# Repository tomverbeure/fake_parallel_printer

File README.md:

# Fake Parallel Printer

This repo contains the design files for the Fake Printer tool: a hardware
dongle with a DB-25 connector that plugs into the parallel printer port
that was available on nearly all computers and equipment in the eighties
and nineties.

Check out this blog post for a detailed description of the design,
and build and usage instructions:

* [Fake Parallel Printer - A Parallel Port Traffic Capturing Tool](https://tomverbeure.github.io/2023/01/24/Fake-Parallel-Printer-Capture-Tool-HW.html)

There are 2 versions of the PCB. Revision 2 only uses 2 layers and doesn't
stick out as much out of the device in which is plugged in. It's probably
the best one to build. The firmware is designed to work for both PCB versions.

## PCB v1

* KiCAD database of the PCB: [`./parallel2usb_v1`](./parallel2usb_v1)
* [Schematic of PCB v1](./parallel2usb_v1/parallel2usb_v1_schematic.pdf)

## PCB v2

**WARNING: v2 hasn't been tested!!!**

* KiCAD database of the PCB: [`./parallel2usb_v2`](./parallel2usb_v2)
* [Schematic of PCB v2](./parallel2usb_v2/parallel2usb_v2_schematic.pdf)

A Digikey cart with all the components to populate version 2 of the PCB can
be found [here](https://www.digikey.com/short/mcb8vf27). Not all
resistors and capacitor must be populated though. Check out the blog
post for details.

## Firmware

[`parallel2usb_hd_on.uf2`](parallel2usb_hd_on.uf2) contains the compiled
firmware for the Raspberry Pico.

To make changes and recompile yourself:

* set the `PICO_SDK` environment variable to the path of your locally installed 
  [Raspberry Pico SDK](https://github.com/raspberrypi/pico-sdk).
* Build the code:

      mkdir -p ./c/build
      cd ./c/build
      cmake ..
      make

* If all goes well, a new `parallel2usb.uf2` will be waiting in
  `./c/build/parallel2usb`.

## Capturing Parallel Port Data

* Plug in the board into the host with the parallel port.
* Connect your PC to the board with a USB cable.
* Run `python3 ./fake_printer.py -p <USB serial device>` (Use -h for more options.)
* Issue a print operation on the host.
* A new file will be generated for each print operation

## Converting a Parallel Port Captured File

* PCL: use [Ghostscript](https://ghostscript.com/releases/gpcldnld.html)

    `~/tools/ghostpcl-10.0.0-linux-x86_64/gpcl6-1000-linux-x86_64 -dNOPAUSE -sOutputFile=output.png -sDEVICE=png256 -g8000x8000 -r600x600 print_cap.pcl`

* Epson ESC/P: use [PrinterToPDF](https://github.com/RWAP/PrinterToPDF)

    `/opt/printerToPDF/bin/printerToPDF -o output -f /opt/printerToPDF/lib/PrinterToPDF/font2/Epson-Standard.C16 print_cap.esc_p`

* Encapsulated Postscript: use Ghostscript and ImageMagick to add a background if necessary.  Note that some scopes (TDS 684B) may emit a few chunks of comments that `fake_printer.py` will get with multiple-second delays, and they need to be concatenated together to form a valid `eps` file.

    `gs -dSAFER -dBATCH -dNOPAUSE -dEPSCrop -sDEVICE=pngalpha -r300 -sOutputFile=ph1-zoomout.png ph1-zoomout.eps; convert -background black -alpha remove -alpha off ph1-zoomout.png ph1-zoomout.png`

# Conversions

* HP Infinium

```
./fake_printer.py --port=/dev/ttyACM0 -t 2 -v --prefix=hp_osc_ -s eps
inkscape -f ./hp_osc_0.eps -w 1580 -y=255 -e hp_osc_0.png
convert hp_osc_0.png -crop 1294x971+142+80 hp_osc_0_cropped.png
```

* Advantest R3273

    * Config printer: Config -> Copy Config -> Printer: 

    * To print: Copy
    * To convert:

```
./fake_printer.py --port=/dev/ttyACM0 -t 2 -v --prefix=r3273_ -s pcl
~/tools/ghostpcl-10.0.0-linux-x86_64/gpcl6-1000-linux-x86_64 -dNOPAUSE -sOutputFile=test.png -sDEVICE=png256 -g8000x8000 -r600x600 r3273_0.pcl
convert test.png -filter point -resize 2000  test2.png
convert test2.png -crop 640x480+315+94 test3.png
```

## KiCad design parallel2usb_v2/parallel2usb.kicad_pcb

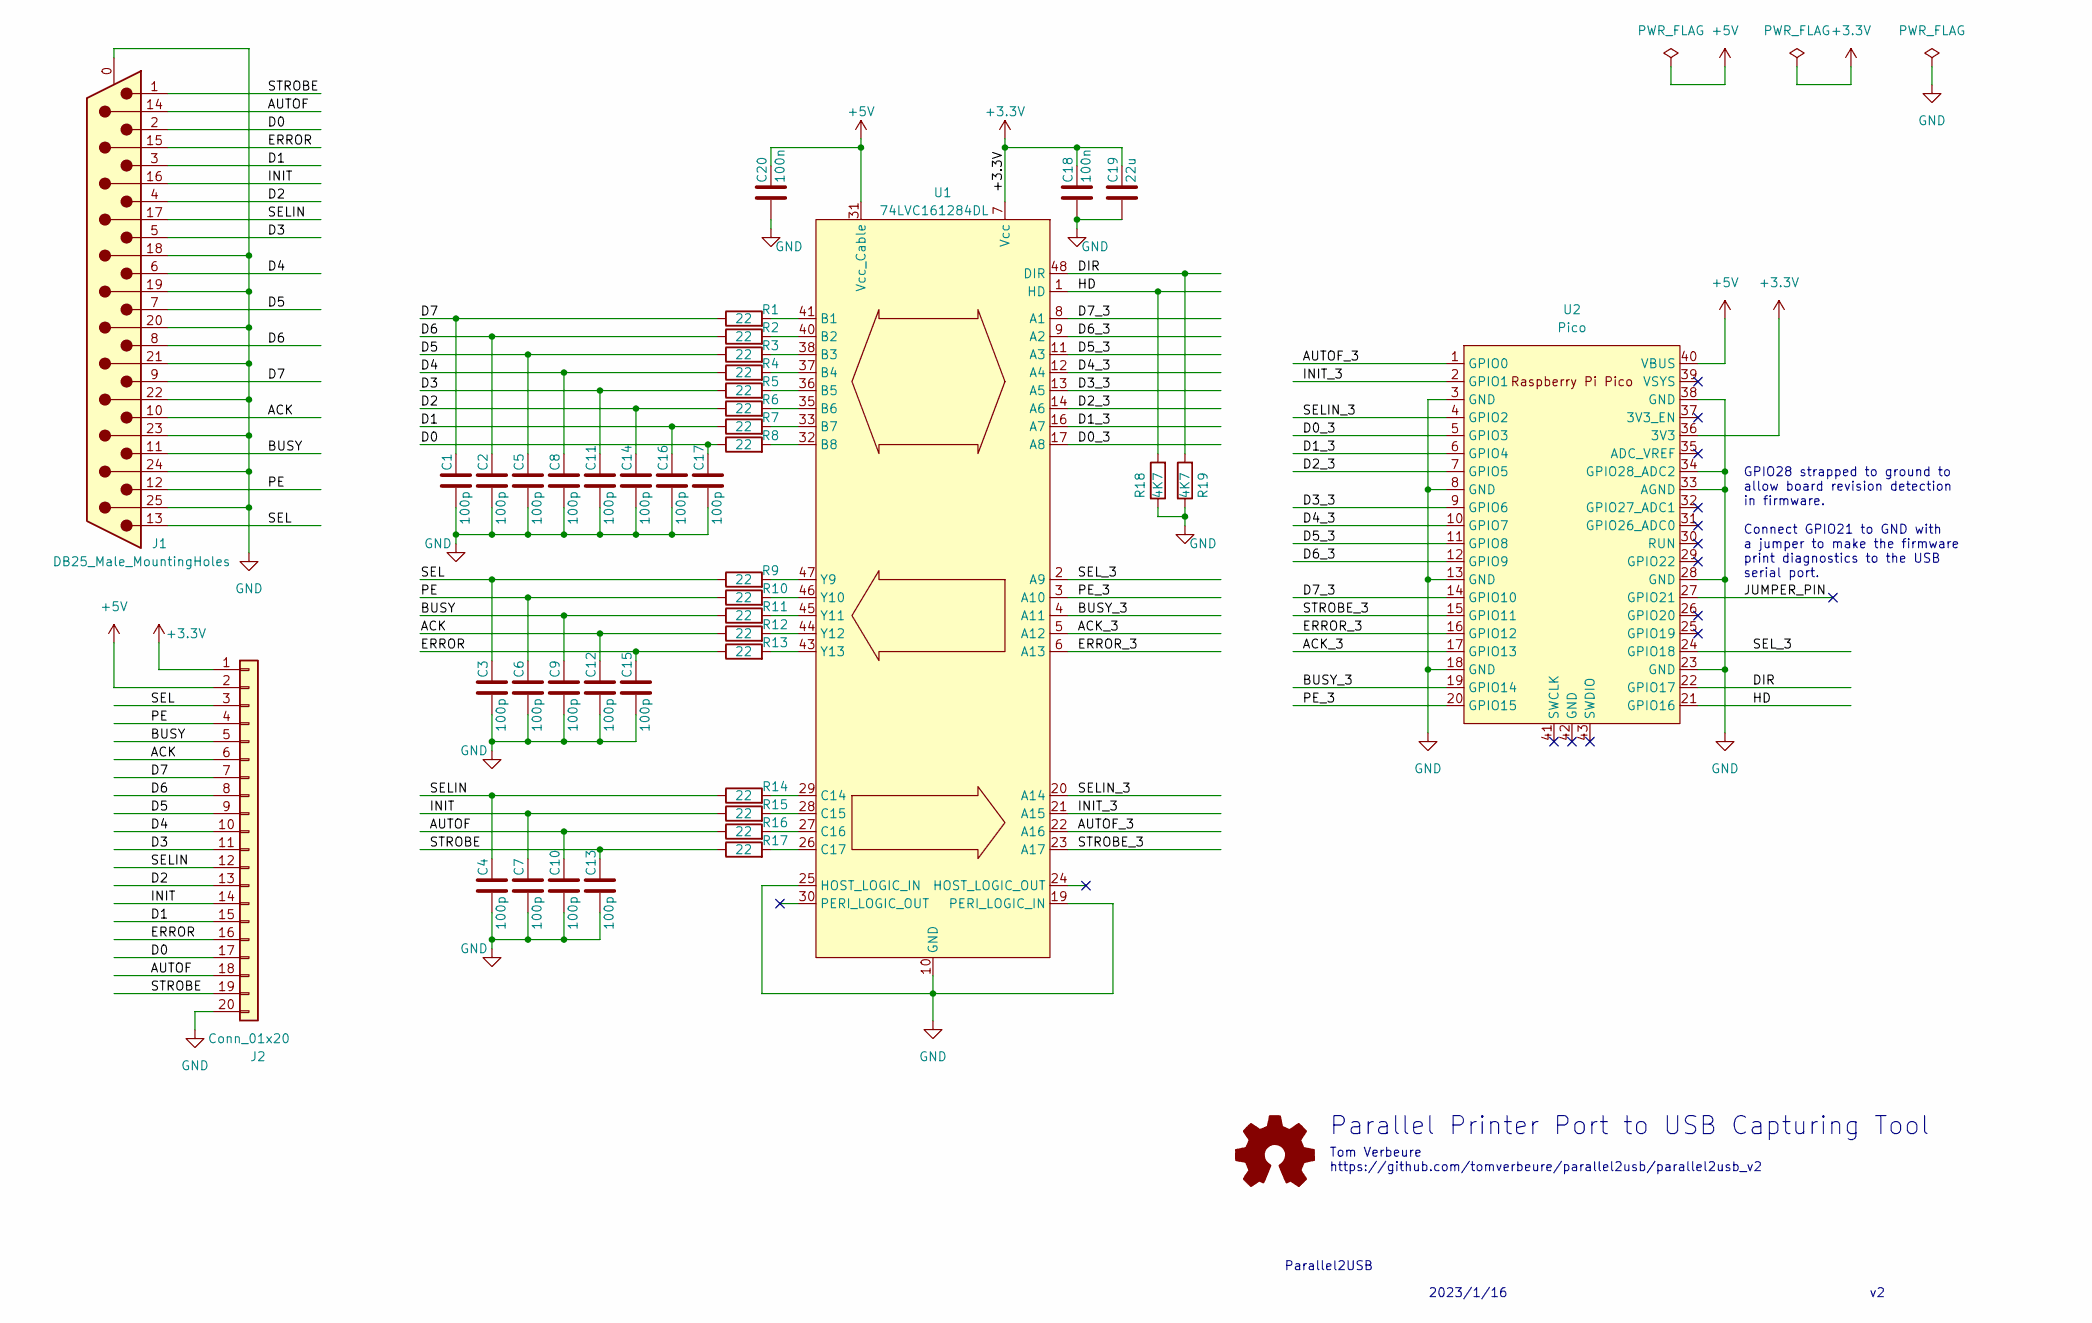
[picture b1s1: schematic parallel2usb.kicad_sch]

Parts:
C1, C2, C3, C4, C5, C6, C7, C8, C9, C10, C11, C12, C13, C14, C15, C16, C17: 100p; C_0603_1608Metric_Pad1.08x0.95mm_HandSolder
C18, C20: 100n; C_0603_1608Metric_Pad1.08x0.95mm_HandSolder
C19: 22u; C_0603_1608Metric_Pad1.08x0.95mm_HandSolder
J1: DB25_Male_MountingHoles; DSUB-25_Male_Horizontal_P2.77x2.84mm_EdgePinOffset7.70mm_Ho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
J2: Conn_01x20; PinHeader_1x20_P2.54mm_Vertical
R1, R2, R3, R4, R5, R6, R7, R8, R9, R10, R11, R12, R13, R14, R15, R16, R17: 22; R_0603_1608Metric_Pad0.98x0.95mm_HandSolder
R18, R19: 4K7; R_0603_1608Metric_Pad0.98x0.95mm_HandSolder
U1: 74LVC161284DL; SSOP-48_7.5x15.9mm_P0.635mm
U2: Pico; RPi_Pico_SMD_TH

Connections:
+3.3V: C18.1, C19.1, J2.1, U1.7 (Vcc), U1.18 (Vcc), U2.36 (3V3)
+5V: C20.1, J2.2, U1.31 (Vcc_Cable), U1.42 (Vcc_Cable), U2.40 (VBUS)
/ACK: C12.1, J1.10, J2.6, R12.1
/ACK_3: U1.5 (A12), U2.17 (GPIO13)
/AUTOF: C10.1, J1.14, J2.18, R16.1
/AUTOF_3: U1.22 (A16), U2.1 (GPIO0)
/BUSY: C9.1, J1.11, J2.5, R11.1
/BUSY_3: U1.4 (A11), U2.19 (GPIO14)
/D0: C17.1, J1.2, J2.17, R8.1
/D0_3: U1.17 (A8), U2.5 (GPIO3)
/D1: C16.1, J1.3, J2.15, R7.1
/D1_3: U1.16 (A7), U2.6 (GPIO4)
/D2: C14.1, J1.4, J2.13, R6.1
/D2_3: U1.14 (A6), U2.7 (GPIO5)
/D3: C11.1, J1.5, J2.11, R5.1
/D3_3: U1.13 (A5), U2.9 (GPIO6)
/D4: C8.1, J1.6, J2.10, R4.1
/D4_3: U1.12 (A4), U2.10 (GPIO7)
/D5: C5.1, J1.7, J2.9, R3.1
/D5_3: U1.11 (A3), U2.11 (GPIO8)
/D6: C2.1, J1.8, J2.8, R2.1
/D6_3: U1.9 (A2), U2.12 (GPIO9)
/D7: C1.1, J1.9, J2.7, R1.1
/D7_3: U1.8 (A1), U2.14 (GPIO10)
/DIR: R19.2, U1.48 (DIR), U2.22 (GPIO17)
/ERROR: C15.1, J1.15, J2.16, R13.1
/ERROR_3: U1.6 (A13), U2.16 (GPIO12)
/HD: R18.2, U1.1 (HD), U2.21 (GPIO16)
/INIT: C7.1, J1.16, J2.14, R15.1
/INIT_3: U1.21 (A15), U2.2 (GPIO1)
/JUMPER_PIN: U2.27 (GPIO21)
/PE: C6.1, J1.12, J2.4, R10.1
/PE_3: U1.3 (A10), U2.20 (GPIO15)
/SEL: C3.1, J1.13, J2.3, R9.1
/SELIN: C4.1, J1.17, J2.12, R14.1
/SELIN_3: U1.20 (A14), U2.4 (GPIO2)
/SEL_3: U1.2 (A9), U2.24 (GPIO18)
/STROBE: C13.1, J1.1, J2.19, R17.1
/STROBE_3: U1.23 (A17), U2.15 (GPIO11)
GND: C1.2, C2.2, C3.2, C4.2, C5.2, C6.2, C7.2, C8.2, C9.2, C10.2, C11.2, C12.2, C13.2, C14.2, C15.2, C16.2, C17.2, C18.2, C19.2, C20.2, J1.0 (PAD), J1.18, J1.19, J1.20, J1.21, J1.22, J1.23, J1.24, J1.25, J2.20, R18.1, R19.1, U1.10 (GND), U1.15 (GND), U1.19 (PERI_LOGIC_IN), U1.25 (HOST_LOGIC_IN), U1.34 (GND), U1.39 (GND), U2.3 (GND), U2.8 (GND), U2.13 (GND), U2.18 (GND), U2.23 (GND), U2.28 (GND), U2.33 (AGND), U2.34 (GPIO28_ADC2), U2.38 (GND)
unnamed: R1.2, U1.41 (B1)
unnamed: R2.2, U1.40 (B2)
unnamed: R3.2, U1.38 (B3)
unnamed: R4.2, U1.37 (B4)
unnamed: R5.2, U1.36 (B5)
unnamed: R6.2, U1.35 (B6)
unnamed: R7.2, U1.33 (B7)
unnamed: R8.2, U1.32 (B8)
unnamed: R9.2, U1.47 (Y9)
unnamed: R10.2, U1.46 (Y10)
unnamed: R11.2, U1.45 (Y11)
unnamed: R12.2, U1.44 (Y12)
unnamed: R13.2, U1.43 (Y13)
unnamed: R14.2, U1.29 (C14)
unnamed: R15.2, U1.28 (C15)
unnamed: R16.2, U1.27 (C16)
unnamed: R17.2, U1.26 (C17)

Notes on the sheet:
Parallel2USB
2023/1/16
Connect GPIO21 to GND with a jumper to make the firmware print diagnostics to the USB serial port.
GPIO28 strapped to ground to allow board revision detection in firmware.
Tom Verbeure https://github.com/tomverbeure/parallel2usb/parallel2usb_v2
Parallel Printer Port to USB Capturing Tool

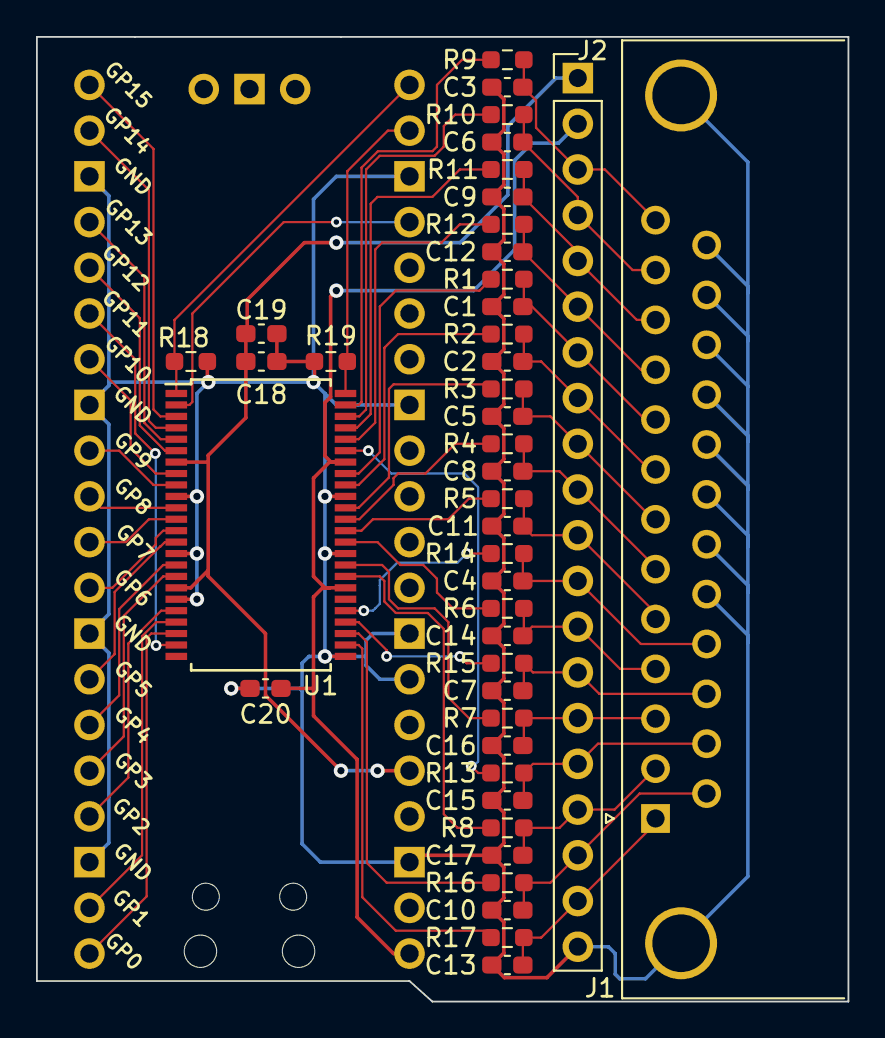
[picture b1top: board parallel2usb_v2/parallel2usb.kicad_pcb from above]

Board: 2 copper layers, 45.1 x 53.6 mm, 43 parts (1 on the bottom side), 56 nets.

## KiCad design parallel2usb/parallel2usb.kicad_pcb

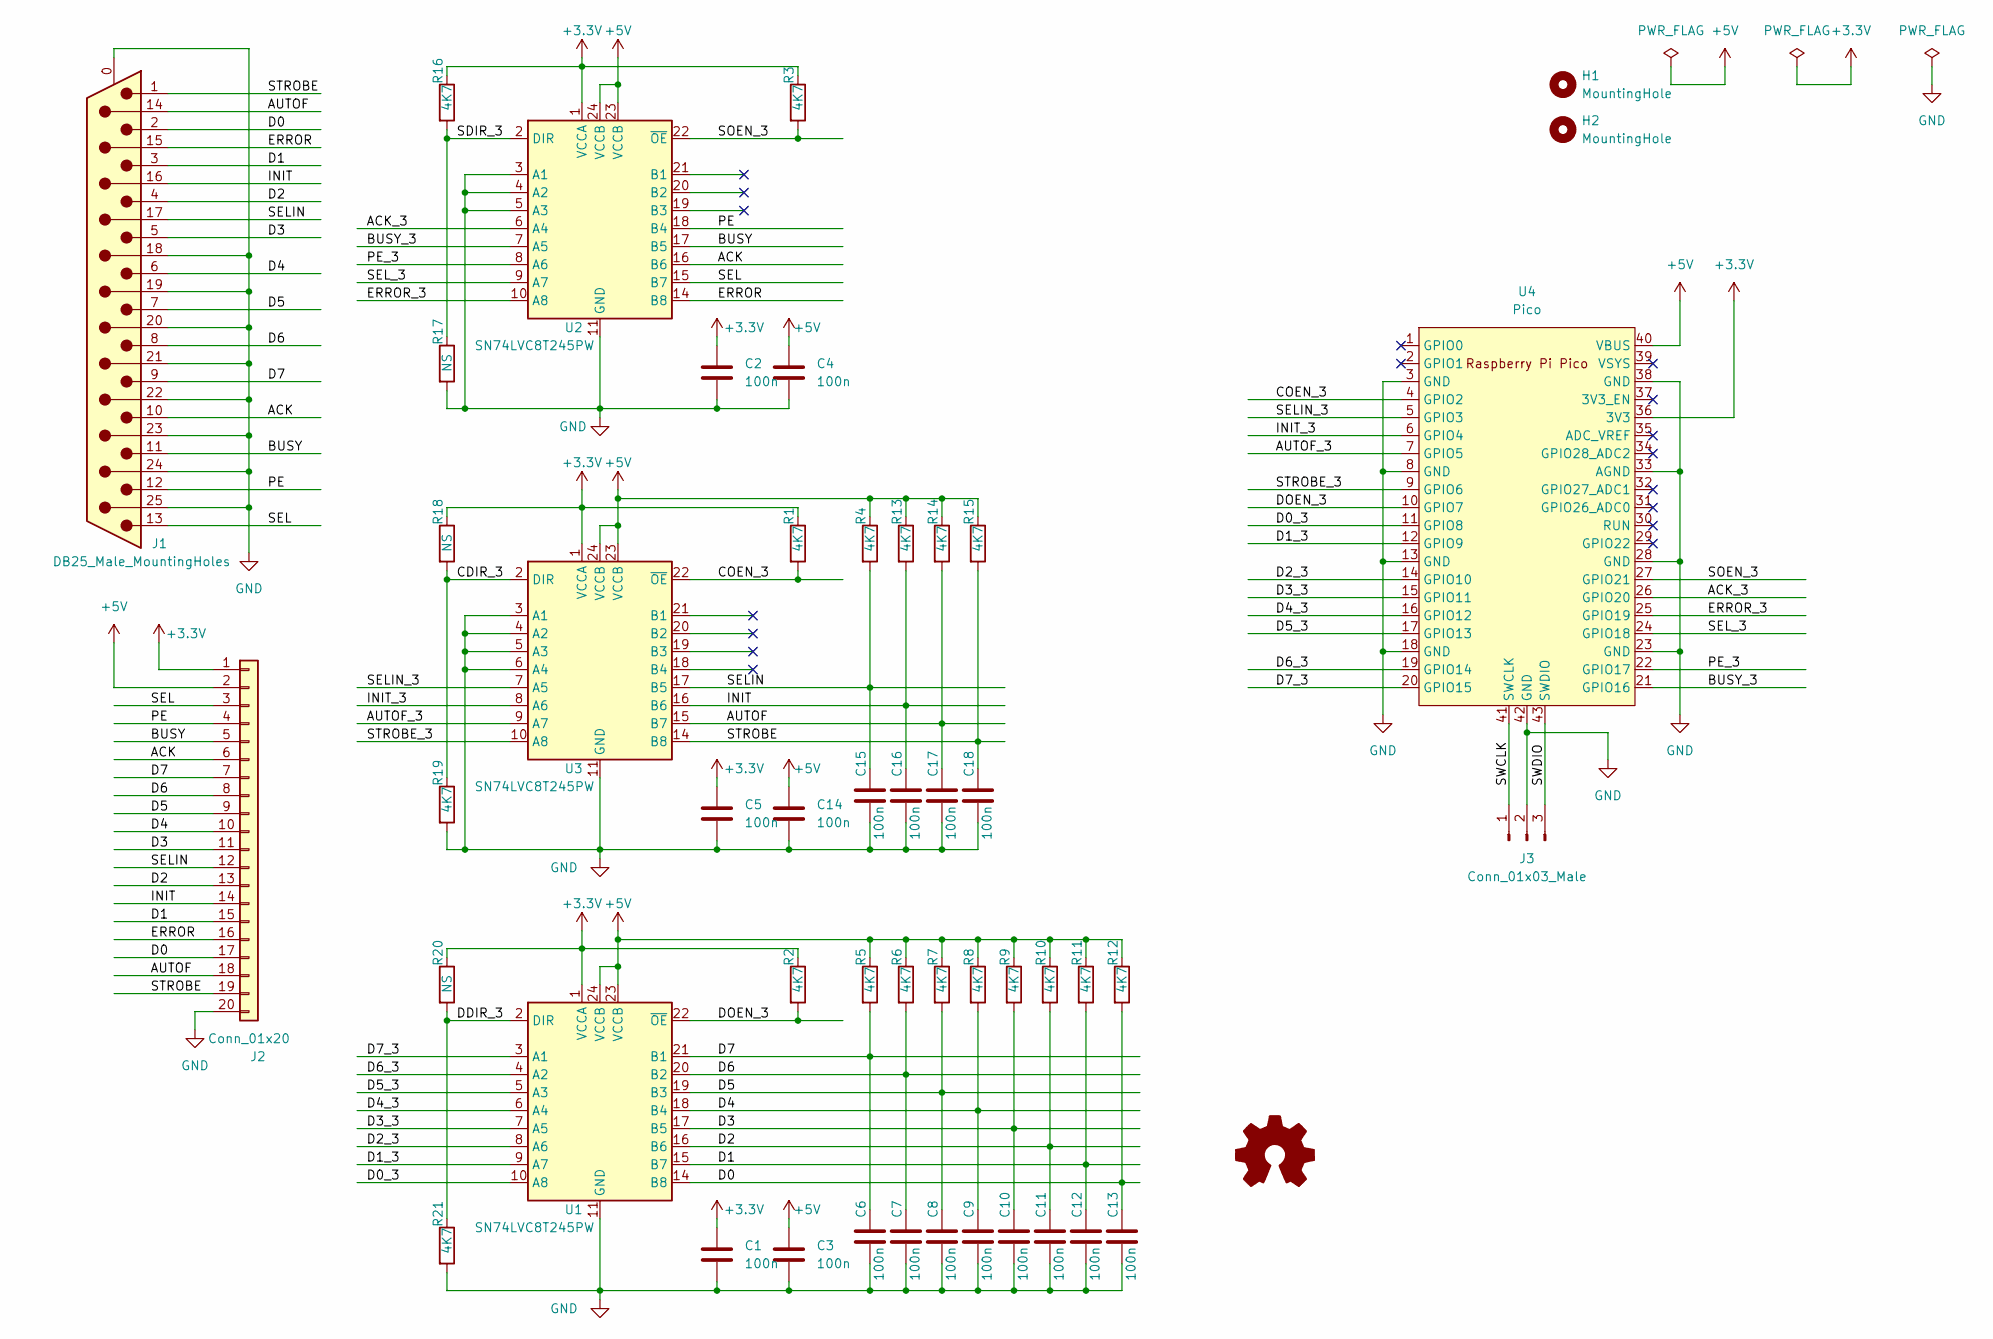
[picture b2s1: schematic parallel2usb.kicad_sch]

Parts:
C1, C2, C3, C4, C5, C6, C7, C8, C9, C10, C11, C12, C13, C14, C15, C16, C17, C18: 100n; C_0603_1608Metric_Pad1.08x0.95mm_HandSolder
H1, H2: MountingHole; MountingHole_2.7mm_M2.5
J1: DB25_Male_MountingHoles; DSUB-25_Male_Horizontal_P2.77x2.84mm_EdgePinOffset7.70mm_Ho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
J2: Conn_01x20; PinHeader_1x20_P2.54mm_Vertical
J3: Conn_01x03_Male; PinHeader_1x03_P2.54mm_Vertical
R1, R2, R3, R4, R5, R6, R7, R8, R9, R10, R11, R12, R13, R14, R15, R16, R19, R21: 4K7; R_0603_1608Metric_Pad0.98x0.95mm_HandSolder
R17, R18, R20: NS; R_0603_1608Metric_Pad0.98x0.95mm_HandSolder
U1, U2, U3: SN74LVC8T245PW; TSSOP-24_4.4x7.8mm_P0.65mm
U4: Pico; RPi_Pico_SMD_TH

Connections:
+3.3V: C1.1, C2.1, C5.1, J2.1, R1.1, R2.1, R3.1, R16.1, R18.1, R20.1, U1.1 (VCCA), U2.1 (VCCA), U3.1 (VCCA), U4.36 (3V3)
+5V: C3.1, C4.1, C14.1, J2.2, R4.1, R5.1, R6.1, R7.1, R8.1, R9.1, R10.1, R11.1, R12.1, R13.1, R14.1, R15.1, U1.23 (VCCB), U1.24 (VCCB), U2.23 (VCCB), U2.24 (VCCB), U3.23 (VCCB), U3.24 (VCCB), U4.40 (VBUS)
/ACK: J1.10, J2.6, U2.16 (B6)
/ACK_3: U2.6 (A4), U4.26 (GPIO20)
/AUTOF: C17.1, J1.14, J2.18, R14.2, U3.15 (B7)
/AUTOF_3: U3.9 (A7), U4.7 (GPIO5)
/BUSY: J1.11, J2.5, U2.17 (B5)
/BUSY_3: U2.7 (A5), U4.21 (GPIO16)
/CDIR_3: R18.2, R19.1, U3.2 (DIR)
/COEN_3: R1.2, U3.22 (~OE), U4.4 (GPIO2)
/D0: C13.1, J1.2, J2.17, R12.2, U1.14 (B8)
/D0_3: U1.10 (A8), U4.11 (GPIO8)
/D1: C12.1, J1.3, J2.15, R11.2, U1.15 (B7)
/D1_3: U1.9 (A7), U4.12 (GPIO9)
/D2: C11.1, J1.4, J2.13, R10.2, U1.16 (B6)
/D2_3: U1.8 (A6), U4.14 (GPIO10)
/D3: C10.1, J1.5, J2.11, R9.2, U1.17 (B5)
/D3_3: U1.7 (A5), U4.15 (GPIO11)
/D4: C9.1, J1.6, J2.10, R8.2, U1.18 (B4)
/D4_3: U1.6 (A4), U4.16 (GPIO12)
/D5: C8.1, J1.7, J2.9, R7.2, U1.19 (B3)
/D5_3: U1.5 (A3), U4.17 (GPIO13)
/D6: C7.1, J1.8, J2.8, R6.2, U1.20 (B2)
/D6_3: U1.4 (A2), U4.19 (GPIO14)
/D7: C6.1, J1.9, J2.7, R5.2, U1.21 (B1)
/D7_3: U1.3 (A1), U4.20 (GPIO15)
/DDIR_3: R20.2, R21.1, U1.2 (DIR)
/DOEN_3: R2.2, U1.22 (~OE), U4.10 (GPIO7)
/ERROR: J1.15, J2.16, U2.14 (B8)
/ERROR_3: U2.10 (A8), U4.25 (GPIO19)
/INIT: C16.1, J1.16, J2.14, R13.2, U3.16 (B6)
/INIT_3: U3.8 (A6), U4.6 (GPIO4)
/PE: J1.12, J2.4, U2.18 (B4)
/PE_3: U2.8 (A6), U4.22 (GPIO17)
/SDIR_3: R16.2, R17.1, U2.2 (DIR)
/SEL: J1.13, J2.3, U2.15 (B7)
/SELIN: C15.1, J1.17, J2.12, R4.2, U3.17 (B5)
/SELIN_3: U3.7 (A5), U4.5 (GPIO3)
/SEL_3: U2.9 (A7), U4.24 (GPIO18)
/SOEN_3: R3.2, U2.22 (~OE), U4.27 (GPIO21)
/STROBE: C18.1, J1.1, J2.19, R15.2, U3.14 (B8)
/STROBE_3: U3.10 (A8), U4.9 (GPIO6)
/SWCLK: J3.1, U4.41 (SWCLK)
/SWDIO: J3.3, U4.43 (SWDIO)
GND: C1.2, C2.2, C3.2, C4.2, C5.2, C6.2, C7.2, C8.2, C9.2, C10.2, C11.2, C12.2, C13.2, C14.2, C15.2, C16.2, C17.2, C18.2, J1.0 (PAD), J1.18, J1.19, J1.20, J1.21, J1.22, J1.23, J1.24, J1.25, J2.20, J3.2, R17.2, R19.2, R21.2, U1.11 (GND), U1.12 (GND), U1.13 (GND), U2.3 (A1), U2.4 (A2), U2.5 (A3), U2.11 (GND), U2.12 (GND), U2.13 (GND), U3.3 (A1), U3.4 (A2), U3.5 (A3), U3.6 (A4), U3.11 (GND), U3.12 (GND), U3.13 (GND), U4.3 (GND), U4.8 (GND), U4.13 (GND), U4.18 (GND), U4.23 (GND), U4.28 (GND), U4.33 (AGND), U4.38 (GND), U4.42 (GND)

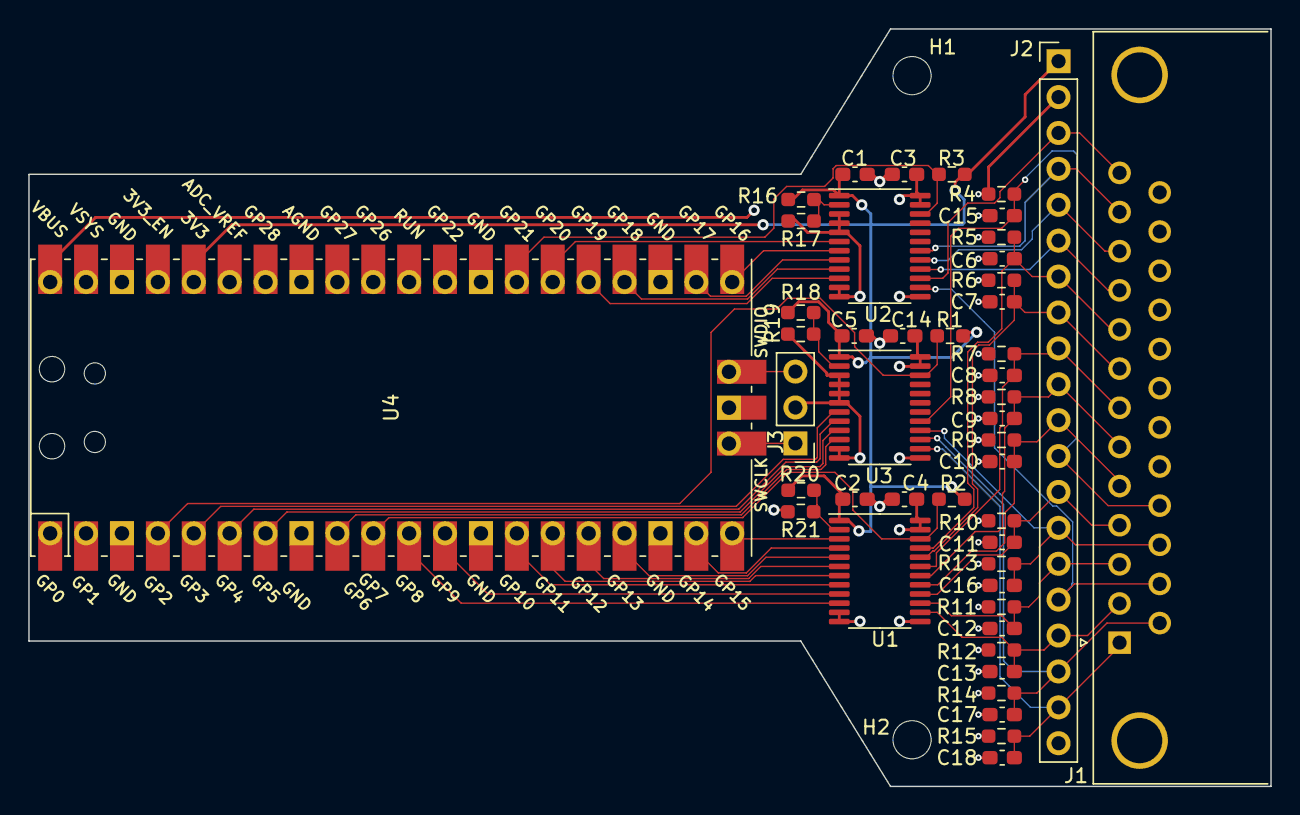
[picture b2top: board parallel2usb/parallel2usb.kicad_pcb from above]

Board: 4 copper layers, 87.9 x 53.6 mm, 48 parts (0 on the bottom side), 45 nets.

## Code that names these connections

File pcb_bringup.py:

# Micropython script to bring up PCV v1.

import board
import digitalio
import time
import supervisor

supervisor.disable_autoreload()

#if False:
#    f = open("test.log", "a")
#    f.write("Hello world!")
#    f.close()

led = digitalio.DigitalInOut(board.LED)
led.direction = digitalio.Direction.OUTPUT

test_pin = digitalio.DigitalInOut(board.GP0)
test_pin.direction = digitalio.Direction.OUTPUT

# high_drive. When 1, outputs are in totem-pole mode, otherwise
# they are in open-drain mode.
hd_pin = digitalio.DigitalInOut(board.GP17)
hd_pin.direction = digitalio.Direction.OUTPUT
hd_pin.value = False

# direction: when high, then direction is from connector to Pico
dir_pin = digitalio.DigitalInOut(board.GP16)
dir_pin.direction = digitalio.Direction.OUTPUT

# For now, test other direction...
dir_pin.value = False

#============================================================
# Control: from host to printer
#============================================================
strobe_pin = digitalio.DigitalInOut(board.GP15)
strobe_pin.direction = digitalio.Direction.INPUT

autof_pin = digitalio.DigitalInOut(board.GP14)
autof_pin.direction = digitalio.Direction.INPUT

init_pin = digitalio.DigitalInOut(board.GP13)
init_pin.direction = digitalio.Direction.INPUT

selin_pin = digitalio.DigitalInOut(board.GP12)
selin_pin.direction = digitalio.Direction.INPUT

#============================================================
# Data: from host to printer
#============================================================

d0_pin = digitalio.DigitalInOut(board.GP11)
d0_pin.direction = digitalio.Direction.INPUT

d1_pin = digitalio.DigitalInOut(board.GP10)
d1_pin.direction = digitalio.Direction.INPUT

d2_pin = digitalio.DigitalInOut(board.GP9)
d2_pin.direction = digitalio.Direction.INPUT

d3_pin = digitalio.DigitalInOut(board.GP8)
d3_pin.direction = digitalio.Direction.INPUT

d4_pin = digitalio.DigitalInOut(board.GP7)
d4_pin.direction = digitalio.Direction.INPUT

d5_pin = digitalio.DigitalInOut(board.GP6)
d5_pin.direction = digitalio.Direction.INPUT

d6_pin = digitalio.DigitalInOut(board.GP5)
d6_pin.direction = digitalio.Direction.INPUT

d7_pin = digitalio.DigitalInOut(board.GP4)
d7_pin.direction = digitalio.Direction.INPUT

#============================================================
# Status: from printer to host
#============================================================
error_pin = digitalio.DigitalInOut(board.GP22)
error_pin.direction = digitalio.Direction.OUTPUT
error_pin.value = False

ack_pin = digitalio.DigitalInOut(board.GP21)
ack_pin.direction = digitalio.Direction.OUTPUT
ack_pin.value   = True

busy_pin = digitalio.DigitalInOut(board.GP20)
busy_pin.direction = digitalio.Direction.OUTPUT
busy_pin.value  = False

pe_pin = digitalio.DigitalInOut(board.GP19)
pe_pin.direction = digitalio.Direction.OUTPUT
pe_pin.value    = True

sel_pin = digitalio.DigitalInOut(board.GP18)
sel_pin.direction = digitalio.Direction.OUTPUT
sel_pin.value   = True

all_inputs = [ d0_pin, d1_pin, d2_pin, d3_pin, d4_pin, d5_pin, d6_pin, d7_pin, strobe_pin, autof_pin, init_pin, selin_pin ]

def test_inputs():
    val = 0
    for i in all_inputs:
        val = (val << 1) | i.value

    print(f"%04x" % (val))

if False:
    led.value = False
    print("1")
    time.sleep(1)
    led.value = True
    print("2")
    time.sleep(1)
    led.value = False
    print("3")
    time.sleep(1)
    led.value = True
    print("4")
   
while False:
    led.value           = True
    test_pin.value      = True
    sel_pin.value       = True
    time.sleep(1)
    test_inputs()
    led.value           = False
    test_pin.value      = False
    sel_pin.value       = False
    time.sleep(1)
    test_inputs()
    pass

def get_data():
    b = ((((((((((((((
            d7_pin.value) << 1) | 
            d6_pin.value) << 1) | 
            d5_pin.value) << 1) | 
            d4_pin.value) << 1) | 
            d3_pin.value) << 1) | 
            d2_pin.value) << 1) | 
            d1_pin.value) << 1) | d0_pin.value

    return b

sel_pin.value   = True
pe_pin.value    = False
ack_pin.value   = True
busy_pin.value  = False
error_pin.value = False

print("Listening...")

time.sleep(0.5)
ack_pin.value   = False
busy_pin.value  = True
error_pin.value  = True
time.sleep(0.5)
ack_pin.value   = True
busy_pin.value  = False
error_pin.value  = True

pe_pin.value = False
error_pin.value  = True

while True:
    print(f"nStrobe: %d, nAUTOF: %d, nINIT: %d, nSELIN: %d, data: %d" % 
            (strobe_pin.value, autof_pin.value, init_pin.value, selin_pin.value, get_data()))

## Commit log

2022-12-31 PCB v1 complete.
2023-01-01 Design with 74LVC161284.
2023-01-15 Checkpoint. First strobe.
2023-01-15 IRQ handler that is too slow.
2023-01-15 Grabs bytes successfully from printer port.
2023-01-15 Example traces.
2023-01-15 Remove old stuff.
2023-01-16 spectrum analyzer printer port traces.
2023-01-17 Clean up code. Add checksum and byte count.
2023-01-17 PCB v2.
2023-01-19 Fix link.
2023-01-19 Add FW support for v1 and v2.
2023-01-19 Minor schematic and gerber updates.
2023-01-21 Deassert BUSY *after* sending data to serial port.
2023-01-21 Add comments about board revision check.
2023-01-24 fake_printer.py script.
2023-01-24 Cleanup examples.
2023-01-24 pcb_bringup.py script.
2023-01-24 All formats of TDS 420A.
2023-01-24 fake_printer extended help.
2023-01-24 r3273 captured traces.
2023-01-24 Add a few flush commands.
2023-01-25 Clean up README.md
2023-01-25 Minor edits.
2023-01-30 Link to blog post.
2023-02-06 Add license.
2023-03-19 Move printer data capturing to core1.
2023-03-19 Update pre-built programming image.
2023-04-23 Conversion instructions.
2023-04-23 Add config image.
2023-04-23 Fix cmd line.
2023-04-23 command line.
2024-04-04 README: add a more reliable conversion flow for EPS
    Inkscape sometimes pops up interactive windows when you try to import EPS, and the command line arguments to Inkscape keep changing. If you just want to rasterize, use Ghostscript as a rasterizer.
